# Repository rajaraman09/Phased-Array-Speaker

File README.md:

# Phased-Array-Speaker

Introduction
For our ECE final project, we designed and built an array of 12 independently-controllable speakers to implement an acoustic phased-array system. 
The system samples a standard audio input signal at approximately 44.1 kHz, and then outputs this signal to each of 12 speakers, each with a variable delay. 
The idea behind a phased-array is that by changing how the speakers are driven the angle of the maximum intensity of the output wave can be shifted. This will be further explored in the high level design of the project.
This type of array was built to be able to support various other more advanced design challenges, including longer-range acoustic modem transmission and sonar imaging.

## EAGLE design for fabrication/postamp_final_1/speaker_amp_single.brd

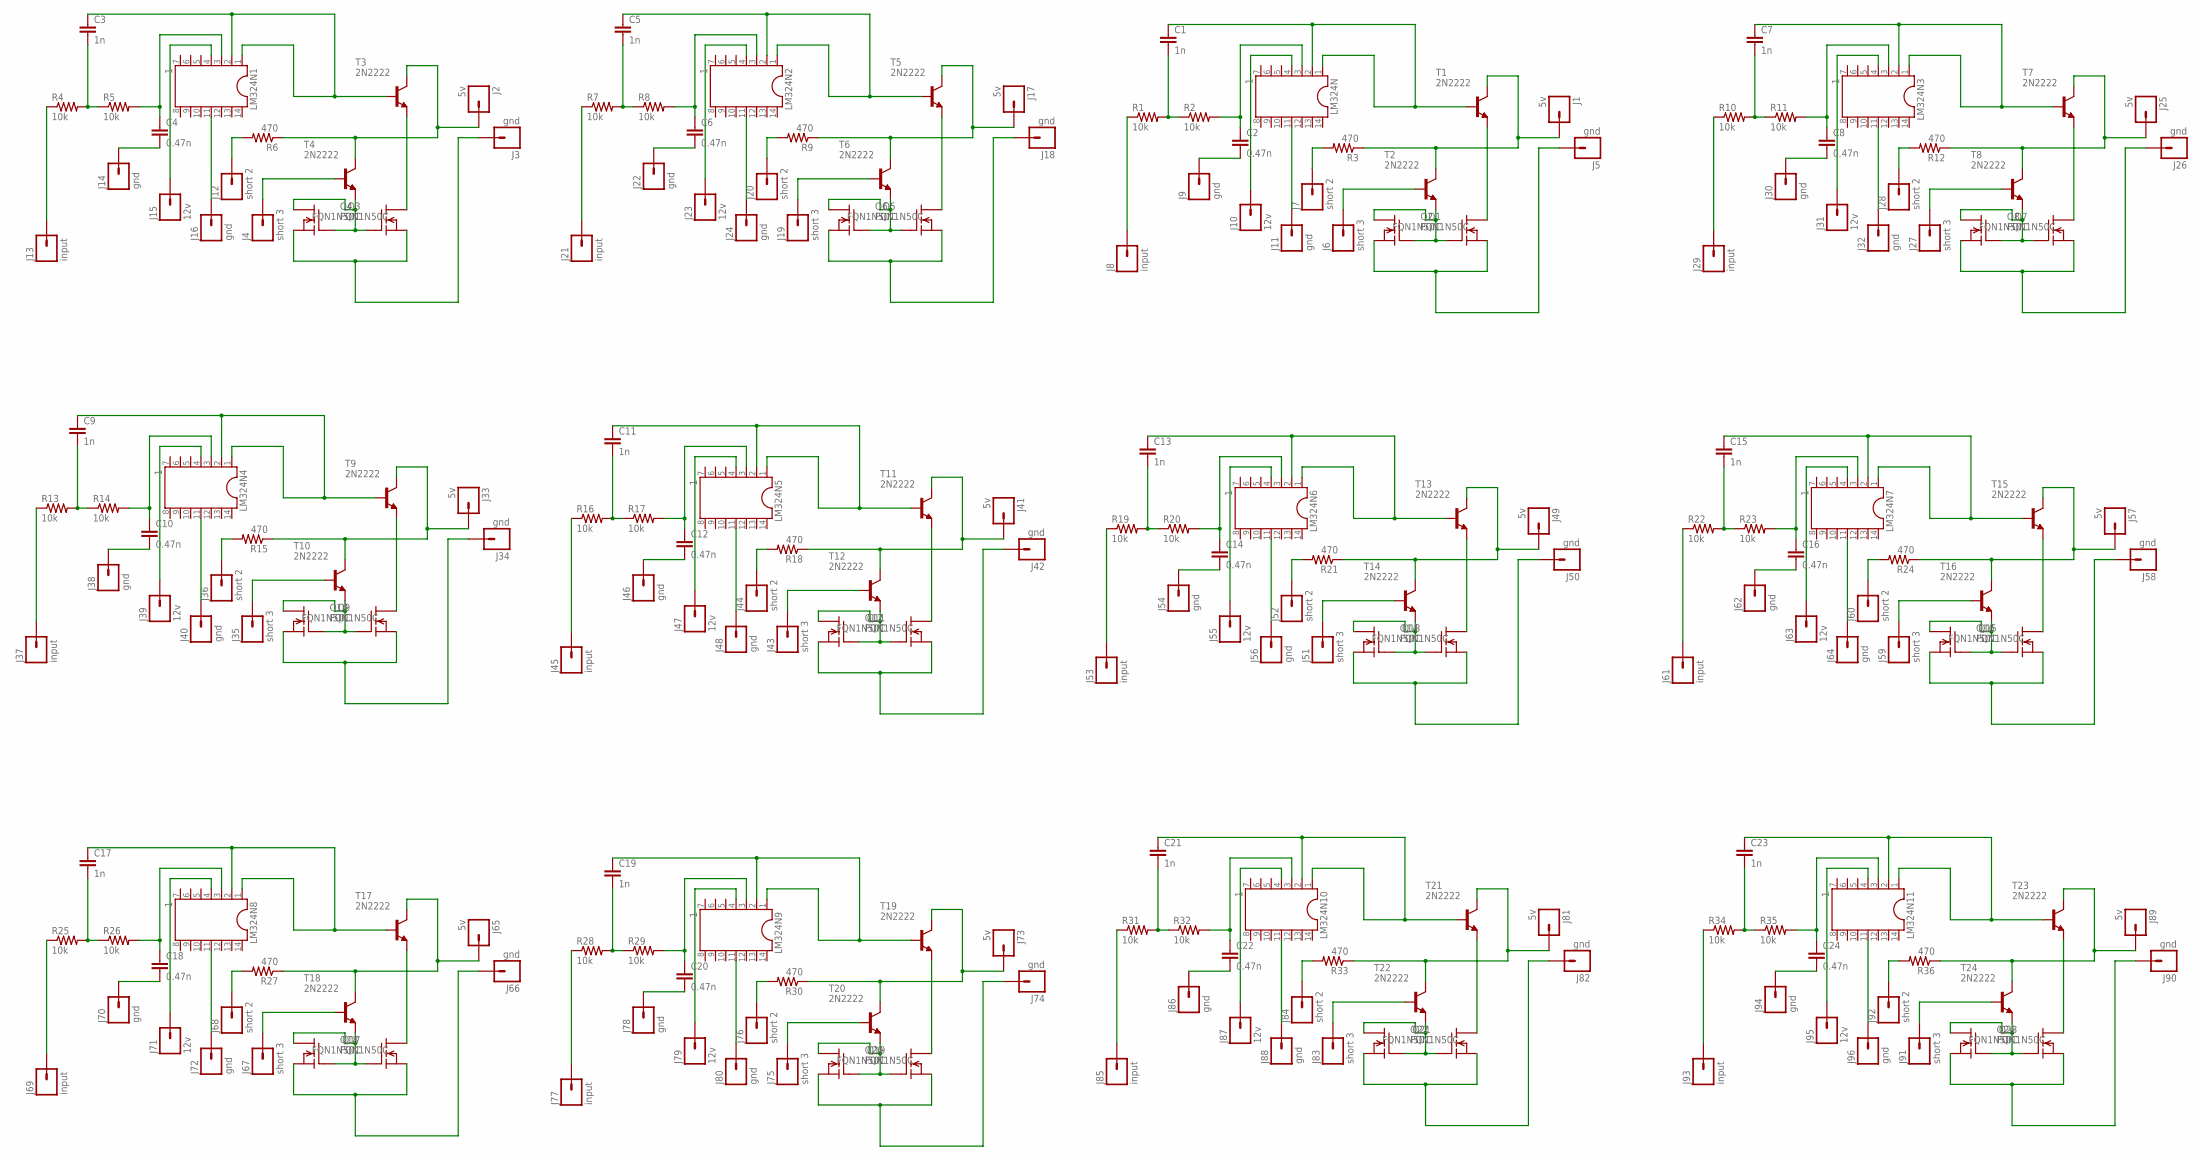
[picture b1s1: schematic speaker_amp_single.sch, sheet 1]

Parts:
C1, C3, C5, C7, C9, C11, C13, C15, C17, C19, C21, C23: 1n; CAP-PTH-SMALL
C2, C4, C6, C8, C10, C12, C14, C16, C18, C20, C22, C24: 0.47n; CAP-PTH-SMALL
J1, J2, J17, J25, J33, J41, J49, J57, J65, J73, J81, J89: 5v; 1X01
J3, J5, J9, J11, J14, J16, J18, J22, J24, J26, J30, J32, J34, J38, J40, J42, J46, J48, J50, J54, J56, J58, J62, J64, J66, J70, J72, J74, J78, J80, J82, J86, J88, J90, J94, J96: gnd; 1X01
J4, J6, J19, J27, J35, J43, J51, J59, J67, J75, J83, J91: short 3; 1X01
J7, J12, J20, J28, J36, J44, J52, J60, J68, J76, J84, J92: short 2; 1X01
J8, J13, J21, J29, J37, J45, J53, J61, J69, J77, J85, J93: input; 1X01
J10, J15, J23, J31, J39, J47, J55, J63, J71, J79, J87, J95: 12v; 1X01
LM324N, LM324N1, LM324N2, LM324N3, LM324N4, LM324N5, LM324N6, LM324N7, LM324N8, LM324N9, LM324N10, LM324N11: 1; DIL14
Q1, Q2, Q3, Q4, Q5, Q6, Q7, Q8, Q9, Q10, Q11, Q12, Q13, Q14, Q15, Q16, Q17, Q18, Q19, Q20, Q21, Q22, Q23, Q24: FQN1N50C; TO92
R1, R2, R4, R5, R7, R8, R10, R11, R13, R14, R16, R17, R19, R20, R22, R23, R25, R26, R28, R29, R31, R32, R34, R35: 10k; AXIAL-0.3
R3, R6, R9, R12, R15, R18, R21, R24, R27, R30, R33, R36: 470; AXIAL-0.3
T1, T2, T3, T4, T5, T6, T7, T8, T9, T10, T11, T12, T13, T14, T15, T16, T17, T18, T19, T20, T21, T22, T23, T24: 2N2222; TO92-EBC-OVAL

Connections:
unnamed: C1.2, R1.P$2 (2), R2.P$1 (1)
unnamed: C2.1, LM324N.3, R2.P$2 (2)
unnamed: C1.1, LM324N.1, LM324N.2, T1.B
unnamed: Q2.2 (D), T1.E
unnamed: Q1.1 (G), Q1.2 (D), Q2.1 (G), T2.E
unnamed: J7.1, R3.P$2 (2)
unnamed: J11.1, LM324N.11
unnamed: J6.1, T2.B
unnamed: J8.1, R1.P$1 (1)
unnamed: J1.1, R3.P$1 (1), T1.C, T2.C
unnamed: C2.2, J9.1
unnamed: J5.1, Q1.3 (S), Q2.3 (S)
unnamed: C3.2, R4.P$2 (2), R5.P$1 (1)
unnamed: J10.1, LM324N.4
unnamed: C4.1, LM324N1.3, R5.P$2 (2)
unnamed: C3.1, LM324N1.1, LM324N1.2, T3.B
unnamed: Q4.2 (D), T3.E
unnamed: Q3.1 (G), Q3.2 (D), Q4.1 (G), T4.E
unnamed: J2.1, R6.P$1 (1), T3.C, T4.C
unnamed: J3.1, Q3.3 (S), Q4.3 (S)
unnamed: J16.1, LM324N1.11
unnamed: J4.1, T4.B
unnamed: J13.1, R4.P$1 (1)
unnamed: C4.2, J14.1
unnamed: J15.1, LM324N1.4
unnamed: J12.1, R6.P$2 (2)
unnamed: C5.2, R7.P$2 (2), R8.P$1 (1)
unnamed: C6.1, LM324N2.3, R8.P$2 (2)
unnamed: C5.1, LM324N2.1, LM324N2.2, T5.B
unnamed: Q6.2 (D), T5.E
unnamed: Q5.1 (G), Q5.2 (D), Q6.1 (G), T6.E
unnamed: J17.1, R9.P$1 (1), T5.C, T6.C
unnamed: J18.1, Q5.3 (S), Q6.3 (S)
unnamed: J24.1, LM324N2.11
unnamed: J19.1, T6.B
unnamed: J21.1, R7.P$1 (1)
unnamed: C6.2, J22.1
unnamed: J23.1, LM324N2.4
unnamed: J20.1, R9.P$2 (2)
unnamed: C7.2, R10.P$2 (2), R11.P$1 (1)
unnamed: C8.1, LM324N3.3, R11.P$2 (2)
unnamed: C7.1, LM324N3.1, LM324N3.2, T7.B
unnamed: Q8.2 (D), T7.E
unnamed: Q7.1 (G), Q7.2 (D), Q8.1 (G), T8.E
unnamed: J25.1, R12.P$1 (1), T7.C, T8.C
unnamed: J26.1, Q7.3 (S), Q8.3 (S)
unnamed: J32.1, LM324N3.11
unnamed: J27.1, T8.B
unnamed: J29.1, R10.P$1 (1)
unnamed: C8.2, J30.1
unnamed: J31.1, LM324N3.4
unnamed: J28.1, R12.P$2 (2)
unnamed: C9.2, R13.P$2 (2), R14.P$1 (1)
unnamed: C10.1, LM324N4.3, R14.P$2 (2)
unnamed: C9.1, LM324N4.1, LM324N4.2, T9.B
unnamed: Q10.2 (D), T9.E
unnamed: Q9.1 (G), Q9.2 (D), Q10.1 (G), T10.E
unnamed: J33.1, R15.P$1 (1), T9.C, T10.C
unnamed: J34.1, Q9.3 (S), Q10.3 (S)
unnamed: J40.1, LM324N4.11
unnamed: J35.1, T10.B
unnamed: J37.1, R13.P$1 (1)
unnamed: C10.2, J38.1
unnamed: J39.1, LM324N4.4
unnamed: J36.1, R15.P$2 (2)
unnamed: C11.2, R16.P$2 (2), R17.P$1 (1)
unnamed: C12.1, LM324N5.3, R17.P$2 (2)
unnamed: C11.1, LM324N5.1, LM324N5.2, T11.B
unnamed: Q12.2 (D), T11.E
unnamed: Q11.1 (G), Q11.2 (D), Q12.1 (G), T12.E
unnamed: J41.1, R18.P$1 (1), T11.C, T12.C
unnamed: J42.1, Q11.3 (S), Q12.3 (S)
unnamed: J48.1, LM324N5.11
unnamed: J43.1, T12.B
unnamed: J45.1, R16.P$1 (1)
unnamed: C12.2, J46.1
unnamed: J47.1, LM324N5.4
unnamed: J44.1, R18.P$2 (2)
unnamed: C13.2, R19.P$2 (2), R20.P$1 (1)
unnamed: C14.1, LM324N6.3, R20.P$2 (2)
unnamed: C13.1, LM324N6.1, LM324N6.2, T13.B
unnamed: Q14.2 (D), T13.E
unnamed: Q13.1 (G), Q13.2 (D), Q14.1 (G), T14.E
unnamed: J49.1, R21.P$1 (1), T13.C, T14.C
unnamed: J50.1, Q13.3 (S), Q14.3 (S)
unnamed: J56.1, LM324N6.11
unnamed: J51.1, T14.B
unnamed: J53.1, R19.P$1 (1)
unnamed: C14.2, J54.1
unnamed: J55.1, LM324N6.4
unnamed: J52.1, R21.P$2 (2)
unnamed: C15.2, R22.P$2 (2), R23.P$1 (1)
unnamed: C16.1, LM324N7.3, R23.P$2 (2)
unnamed: C15.1, LM324N7.1, LM324N7.2, T15.B
unnamed: Q16.2 (D), T15.E
unnamed: Q15.1 (G), Q15.2 (D), Q16.1 (G), T16.E
unnamed: J57.1, R24.P$1 (1), T15.C, T16.C
unnamed: J58.1, Q15.3 (S), Q16.3 (S)
unnamed: J64.1, LM324N7.11
unnamed: J59.1, T16.B
unnamed: J61.1, R22.P$1 (1)
unnamed: C16.2, J62.1
unnamed: J63.1, LM324N7.4
unnamed: J60.1, R24.P$2 (2)
unnamed: C17.2, R25.P$2 (2), R26.P$1 (1)
unnamed: C18.1, LM324N8.3, R26.P$2 (2)
unnamed: C17.1, LM324N8.1, LM324N8.2, T17.B
unnamed: Q18.2 (D), T17.E
unnamed: Q17.1 (G), Q17.2 (D), Q18.1 (G), T18.E
unnamed: J65.1, R27.P$1 (1), T17.C, T18.C
unnamed: J66.1, Q17.3 (S), Q18.3 (S)
unnamed: J72.1, LM324N8.11
unnamed: J67.1, T18.B
unnamed: J69.1, R25.P$1 (1)
unnamed: C18.2, J70.1
unnamed: J71.1, LM324N8.4
unnamed: J68.1, R27.P$2 (2)
unnamed: C19.2, R28.P$2 (2), R29.P$1 (1)
unnamed: C20.1, LM324N9.3, R29.P$2 (2)
unnamed: C19.1, LM324N9.1, LM324N9.2, T19.B
unnamed: Q20.2 (D), T19.E
unnamed: Q19.1 (G), Q19.2 (D), Q20.1 (G), T20.E
unnamed: J73.1, R30.P$1 (1), T19.C, T20.C
unnamed: J74.1, Q19.3 (S), Q20.3 (S)
unnamed: J80.1, LM324N9.11
unnamed: J75.1, T20.B
unnamed: J77.1, R28.P$1 (1)
unnamed: C20.2, J78.1
unnamed: J79.1, LM324N9.4
unnamed: J76.1, R30.P$2 (2)
unnamed: C21.2, R31.P$2 (2), R32.P$1 (1)
unnamed: C22.1, LM324N10.3, R32.P$2 (2)
unnamed: C21.1, LM324N10.1, LM324N10.2, T21.B
unnamed: Q22.2 (D), T21.E
unnamed: Q21.1 (G), Q21.2 (D), Q22.1 (G), T22.E
unnamed: J81.1, R33.P$1 (1), T21.C, T22.C
unnamed: J82.1, Q21.3 (S), Q22.3 (S)
unnamed: J88.1, LM324N10.11
unnamed: J83.1, T22.B
unnamed: J85.1, R31.P$1 (1)
unnamed: C22.2, J86.1
unnamed: J87.1, LM324N10.4
unnamed: J84.1, R33.P$2 (2)
unnamed: C23.2, R34.P$2 (2), R35.P$1 (1)
unnamed: C24.1, LM324N11.3, R35.P$2 (2)
unnamed: C23.1, LM324N11.1, LM324N11.2, T23.B
unnamed: Q24.2 (D), T23.E
unnamed: Q23.1 (G), Q23.2 (D), Q24.1 (G), T24.E
unnamed: J89.1, R36.P$1 (1), T23.C, T24.C
unnamed: J90.1, Q23.3 (S), Q24.3 (S)
unnamed: J96.1, LM324N11.11
unnamed: J91.1, T24.B
unnamed: J93.1, R34.P$1 (1)
unnamed: C24.2, J94.1
unnamed: J95.1, LM324N11.4
unnamed: J92.1, R36.P$2 (2)

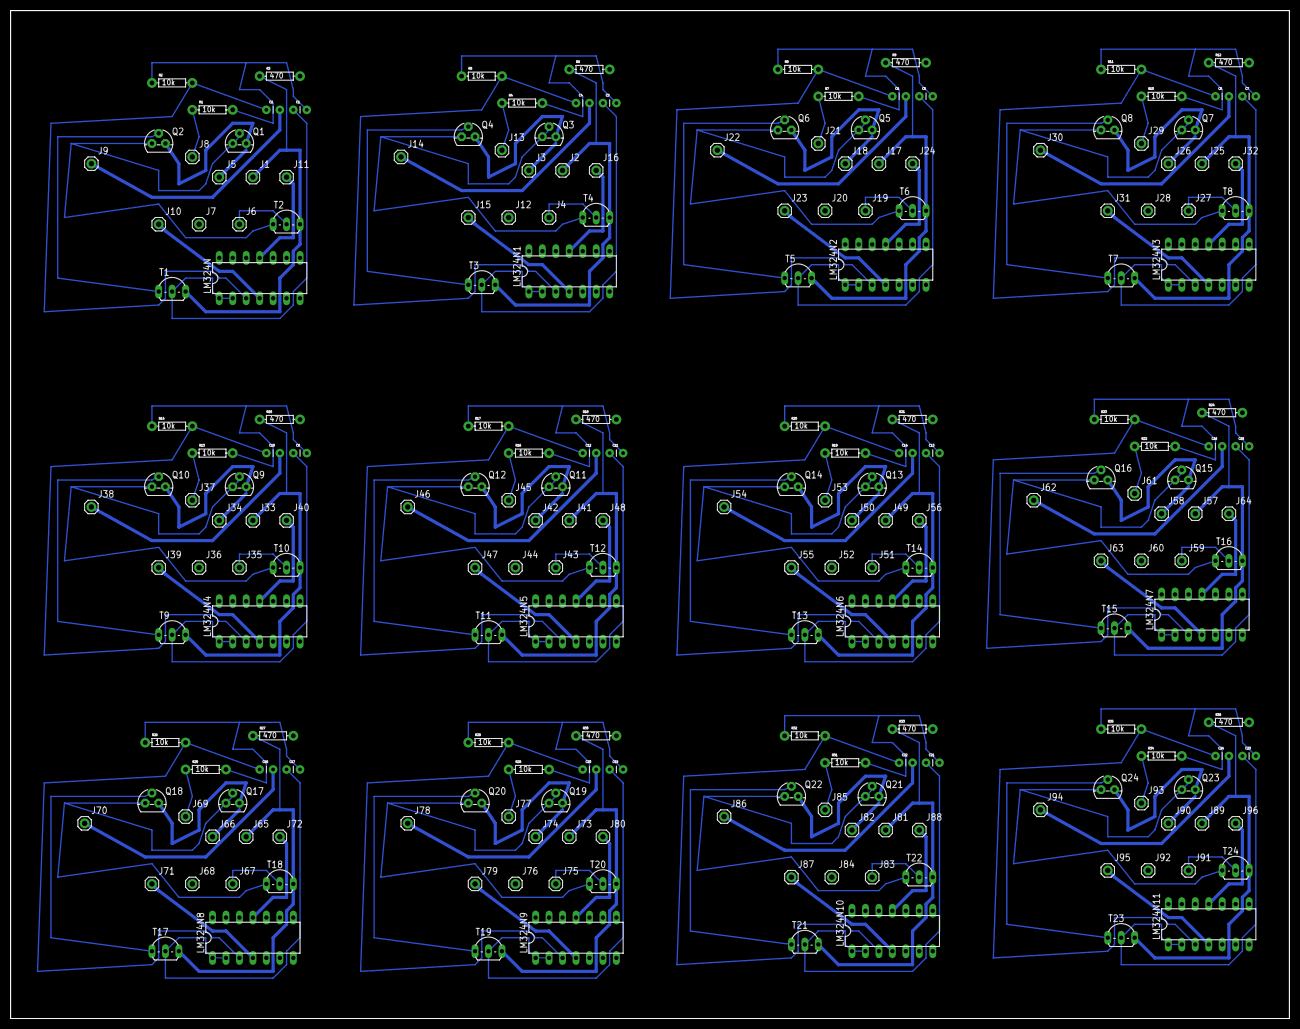
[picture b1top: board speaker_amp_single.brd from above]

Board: 2 copper layers, 241.3 x 190.2 mm, 216 parts (0 on the bottom side), 156 nets.

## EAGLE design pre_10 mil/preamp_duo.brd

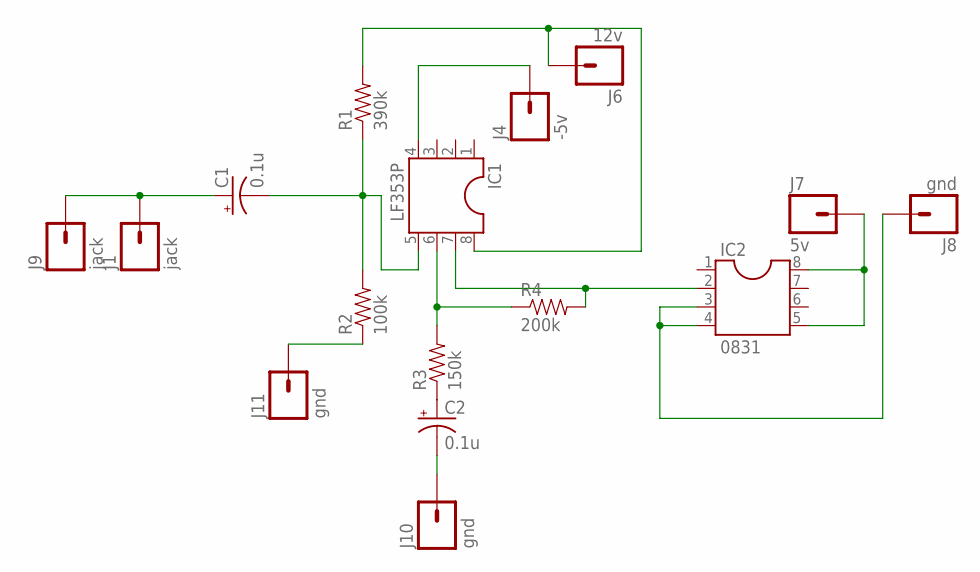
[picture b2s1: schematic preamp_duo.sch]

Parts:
C1, C2: 0.1u; CPOL-RADIAL-10UF-25V
IC1: LF353P; DIL08
IC2: 0831; DIL08
J1, J9: jack; 1X01
J4: -5v; 1X01
J6: 12v; 1X01
J7: 5v; 1X01
J8, J10, J11: gnd; 1X01
R1: 390k; AXIAL-0.3
R2: 100k; AXIAL-0.3
R3: 150k; AXIAL-0.3
R4: 200k; AXIAL-0.3

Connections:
unnamed: C1.2 (-), IC1.5, R1.P$1 (1), R2.P$2 (2)
unnamed: C1.1 (+), J1.1, J9.1
unnamed: IC1.8, J6.1, R1.P$2 (2)
unnamed: C2.1 (+), R3.P$1 (1)
unnamed: IC1.6, R3.P$2 (2), R4.P$1 (1)
unnamed: IC1.7, IC2.2, R4.P$2 (2)
unnamed: IC1.4, J4.1
unnamed: IC2.5, IC2.8, J7.1
unnamed: J11.1, R2.P$1 (1)
unnamed: IC2.3, IC2.4, J8.1
unnamed: C2.2 (-), J10.1

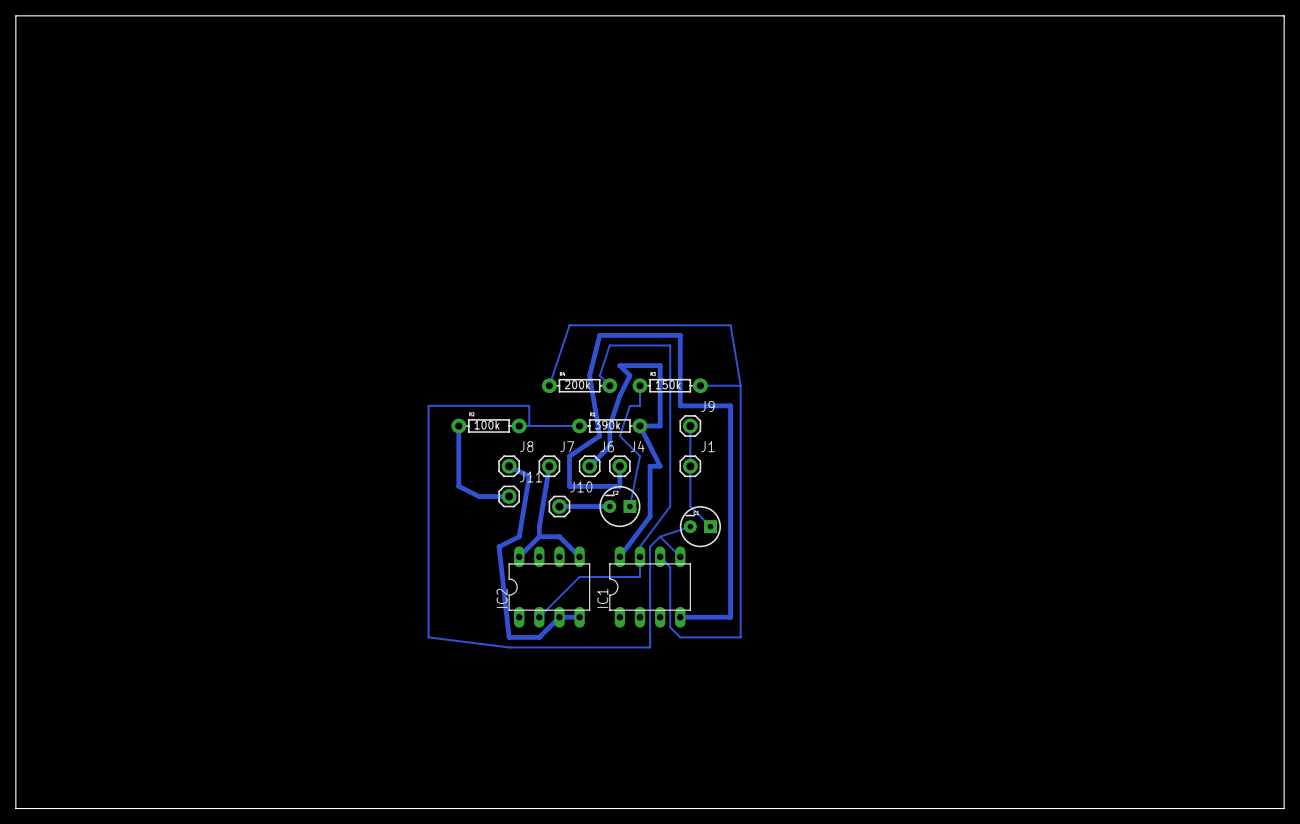
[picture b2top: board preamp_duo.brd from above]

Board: 2 copper layers, 160.0 x 100.0 mm, 16 parts (0 on the bottom side), 11 nets.

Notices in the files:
parts and their libraries:
SparkFun-Resistors: Licensing: Creative Commons ShareAlike 4.0 International - https://creativecommons.org/licenses/by-sa/4.0
